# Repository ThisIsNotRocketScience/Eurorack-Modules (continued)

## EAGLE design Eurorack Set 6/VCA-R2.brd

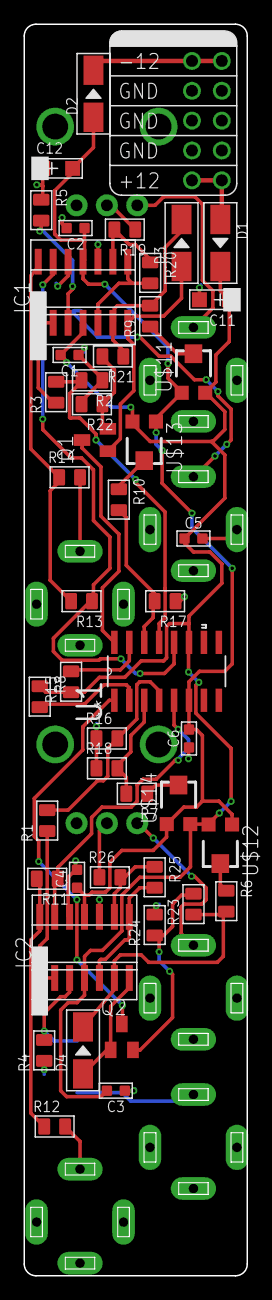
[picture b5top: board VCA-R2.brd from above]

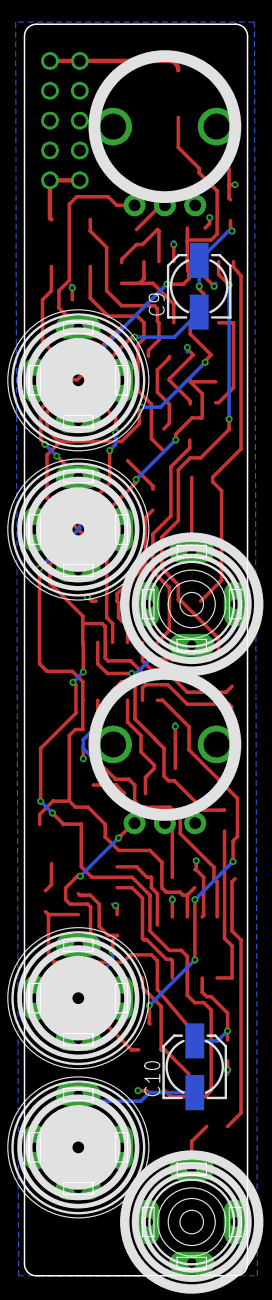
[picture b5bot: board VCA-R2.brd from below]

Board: 2 copper layers, 19.0 x 106.5 mm, 59 parts (11 on the bottom side), 43 nets.

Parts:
C1, C2, C3, C4, C5, C6: 100nF; C0603
C9, C10: 1uF-BIDIR; 153CLV-0505
C11, C12: 10uF; AVX-A
D1, D2, D3, D4: MRA4004T3G; DO-214AC
IC1, IC2: TL074D; SO14
Q1, Q2: MMBT3906LT1SMD; SOT23-BEC
R1, R3: 49.9K; C0805
R2, R16, R17, R18: 499; C0805
R4, R5, R6, R7, R9, R10: 220K; C0805
R8, R15: 249K; C0805
R11, R13: 30.1K; C0805
R12, R14: 100; C0805
R19, R26: 100K; C0805
R20, R21, R23, R25: 2K; C0805
R22, R24: 200; C0805
U1: LM13700M; SOIC127P620X175-16N
U$1: EURORACK_PCB4HP; EURORACK4HPPCB
U$2, U$3: 100K; OG-POTS_ALPS_POT_VERTICAL
U$4, U$5, U$6, U$7: PJ-341; 3.5MM-JACK-SWITCH-13MM-INPUT
U$8, U$9: PJ-341; 3.5MM-JACK-SWITCH-13MM-OUTPUT
U$10: POWER_SIMPLE10; POWER_10
U$11, U$12, U$13, U$14: 100K; TC33X

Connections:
12V: C1.2, C3.2, C5.1, C11.+, D1.2, IC1.4, IC2.4, R8.1, R15.1, U1.11, U$11.3, U$12.3, U$13.3, U$14.3
-12V: C2.1, C4.1, C6.2, C12.-, D2.1, IC1.11, IC2.11, U1.6, U$11.1, U$12.1, U$13.1, U$14.1
CV_IN_A: Q1.C, U1.16
CV_IN_B: Q2.C, U1.1
GND: C1.1, C2.2, C3.1, C4.2, C5.2, C6.1, C11.-, C12.+, IC1.10, IC1.12, IC2.10, IC2.12, R2.1, R4.1, R5.1, R16.1, R17.1, R18.1, R22.2, R24.2, U$2.P$3, U$3.P$3, U$4.RING@3, U$4.SWITCH@3, U$5.RING@3, U$5.SWITCH@3, U$6.RING@3, U$6.SWITCH@3, U$7.RING@3, U$7.SWITCH@3, U$8.RING@3, U$9.RING@3, U$10.3, U$10.4, U$10.5, U$10.6, U$10.7, U$10.8
unnamed: R14.2, U$8.TIP@3
unnamed: IC1.14, R13.2, R14.1
unnamed: R8.2, U1.2
unnamed: R15.2, U1.15
unnamed: R12.2, U$9.TIP@3
unnamed: IC2.14, R11.2, R12.1
unnamed: R19.1, U$2.P$2
unnamed: R10.1, U$13.2
unnamed: R9.1, U$11.2
unnamed: R7.1, U$14.2
unnamed: R6.1, U$12.2
unnamed: C9.-, U$4.TIP@3
unnamed: C10.-, U$6.TIP@3
unnamed: C9.+, IC1.3, R5.2
unnamed: C10.+, IC2.3, R4.2
unnamed: IC1.1, IC1.2, R3.1
unnamed: IC2.1, IC2.2, R1.1
unnamed: R2.2, R3.2, U1.13
unnamed: R1.2, R16.2, U1.4
unnamed: R10.2, R17.2, U1.14
unnamed: U$3.P$1, U$7.TIP@3
unnamed: R7.2, R18.2, U1.3
unnamed: U$2.P$1, U$5.TIP@3
unnamed: IC1.9, R19.2, R20.1
unnamed: IC1.5, IC1.8, R20.2
unnamed: D3.2, IC1.6, R9.2, R21.1
unnamed: D1.1, U$10.9, U$10.10
unnamed: D3.1, IC1.7, Q1.B
unnamed: Q1.E, R21.2, R22.1
unnamed: D4.2, IC2.6, R6.2, R23.1
unnamed: D4.1, IC2.7, Q2.B
unnamed: Q2.E, R23.2, R24.1
unnamed: IC2.5, IC2.8, R25.2
unnamed: R26.1, U$3.P$2
unnamed: IC2.9, R25.1, R26.2
unnamed: D2.2, U$10.1, U$10.2
TRANS_OUT_A: IC1.13, R13.1, U1.12
TRANS_OUT_B: IC2.13, R11.1, U1.5

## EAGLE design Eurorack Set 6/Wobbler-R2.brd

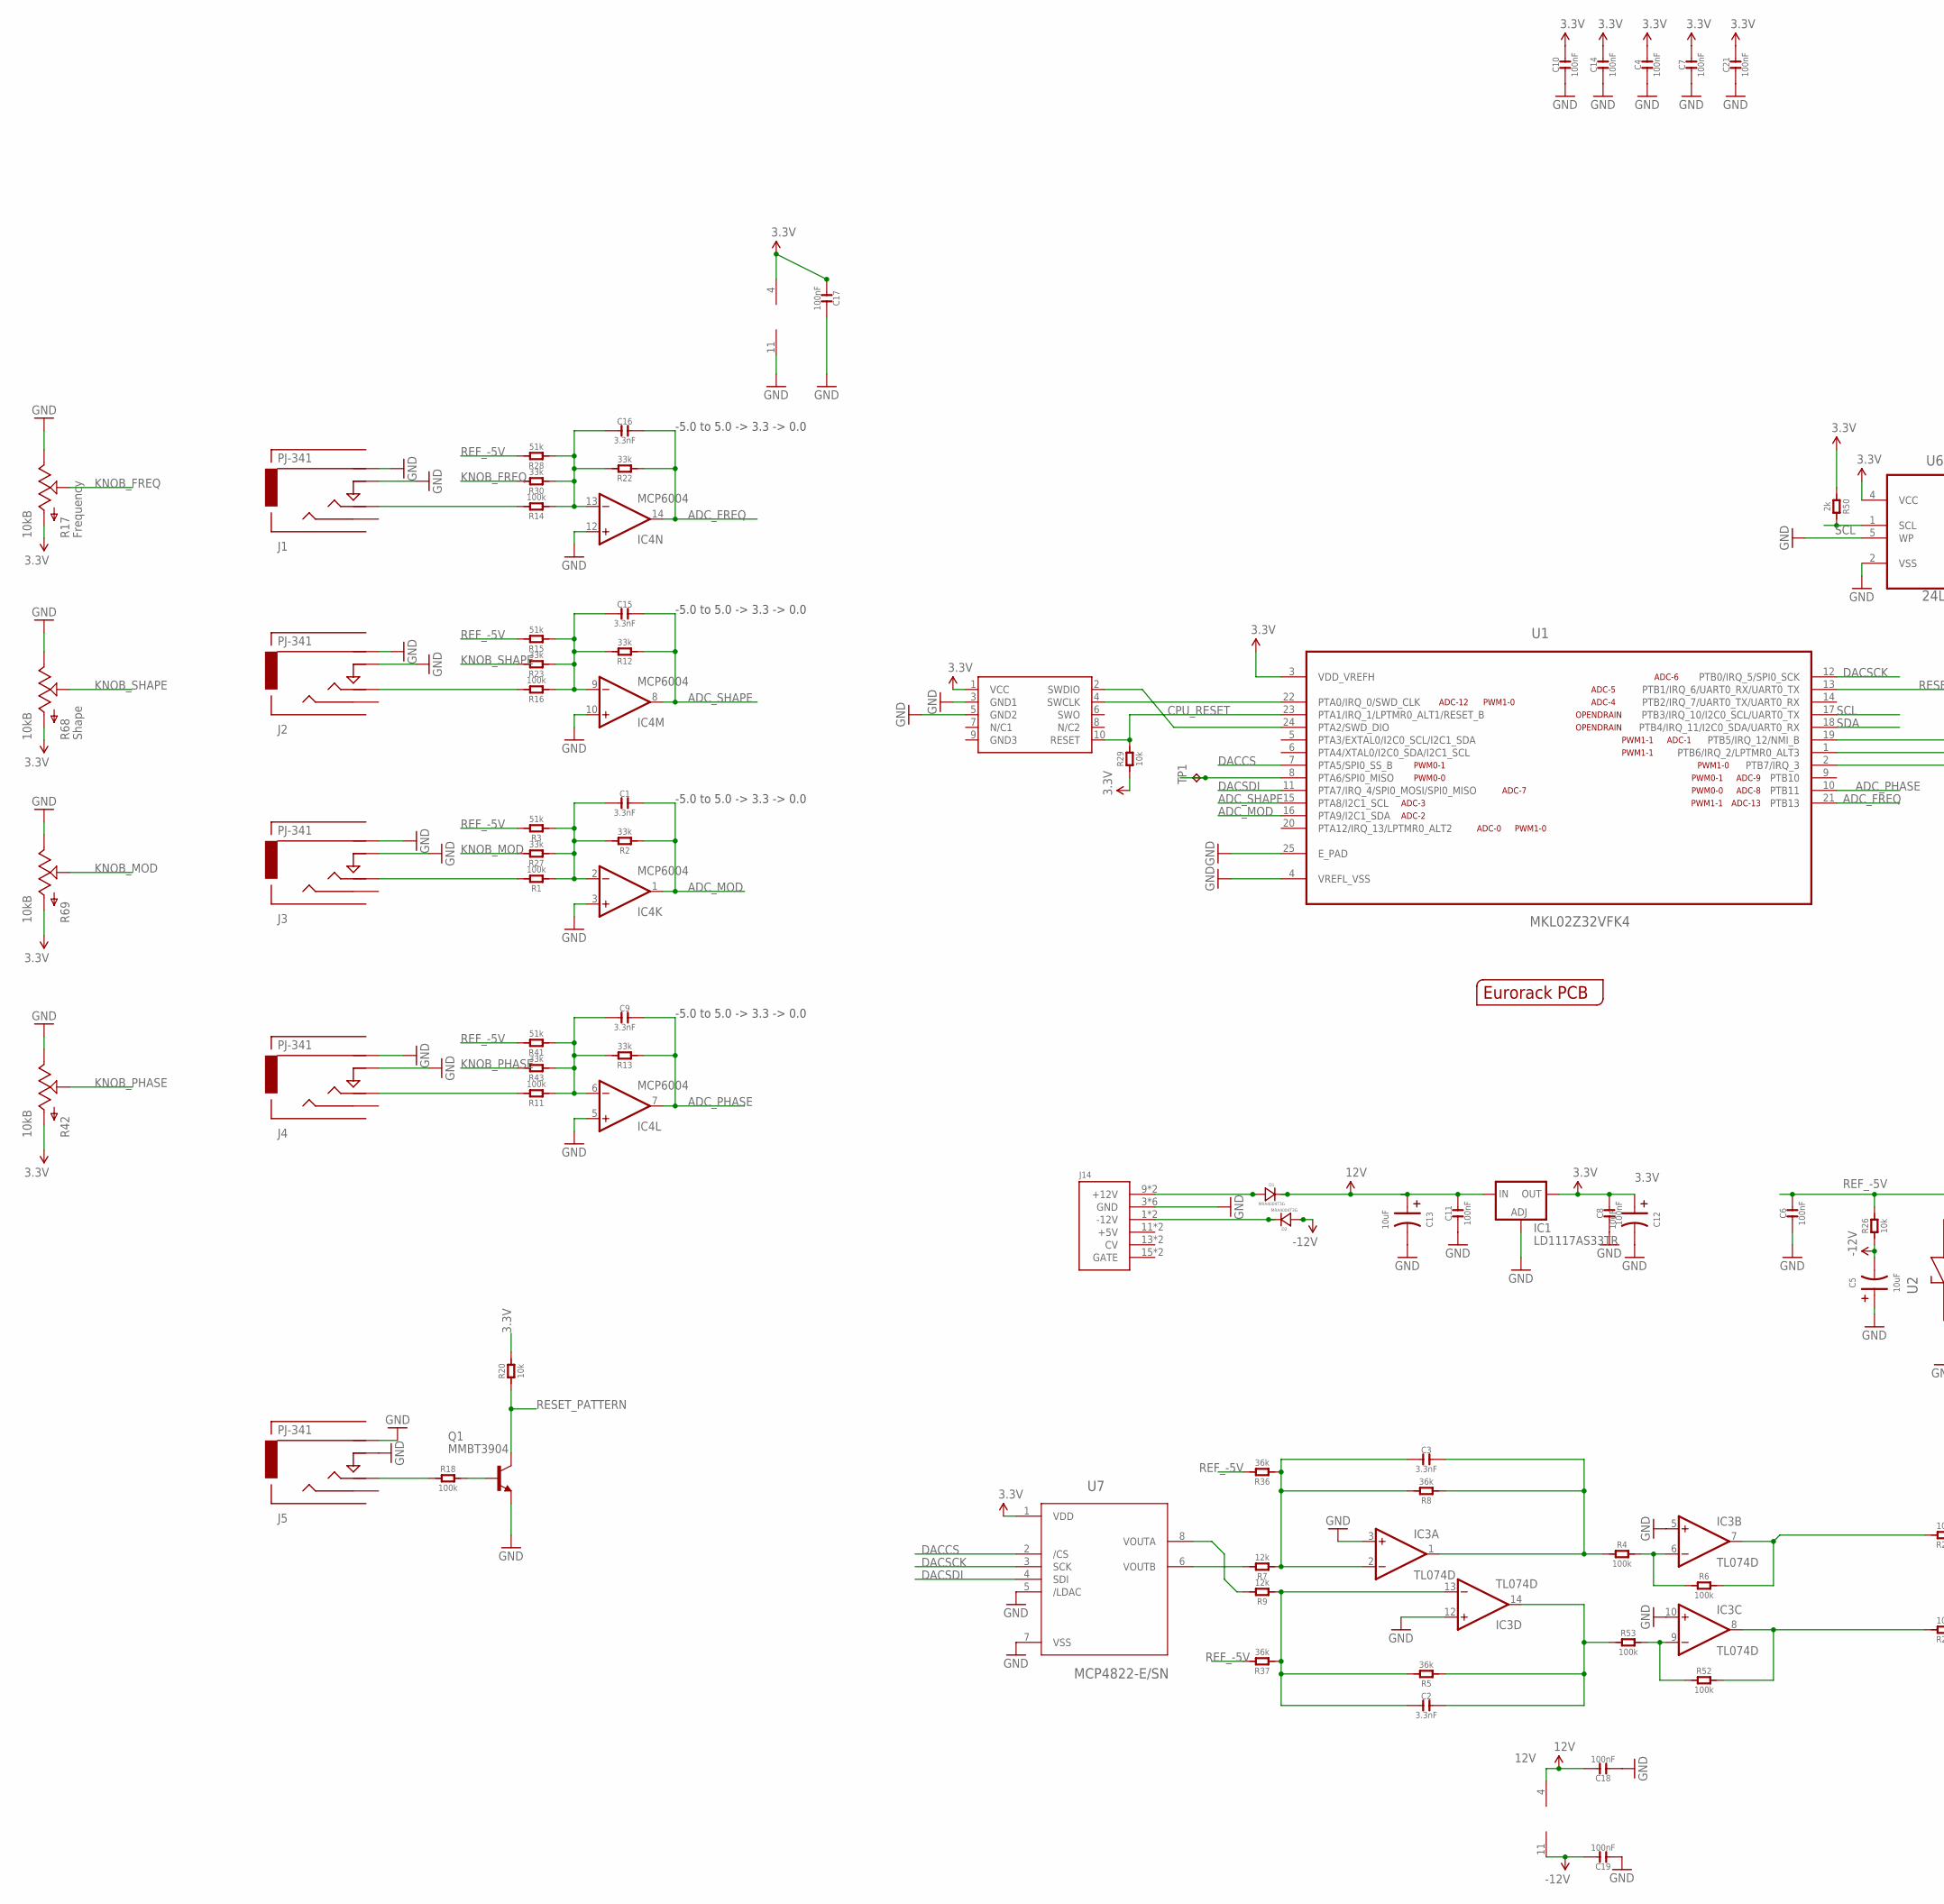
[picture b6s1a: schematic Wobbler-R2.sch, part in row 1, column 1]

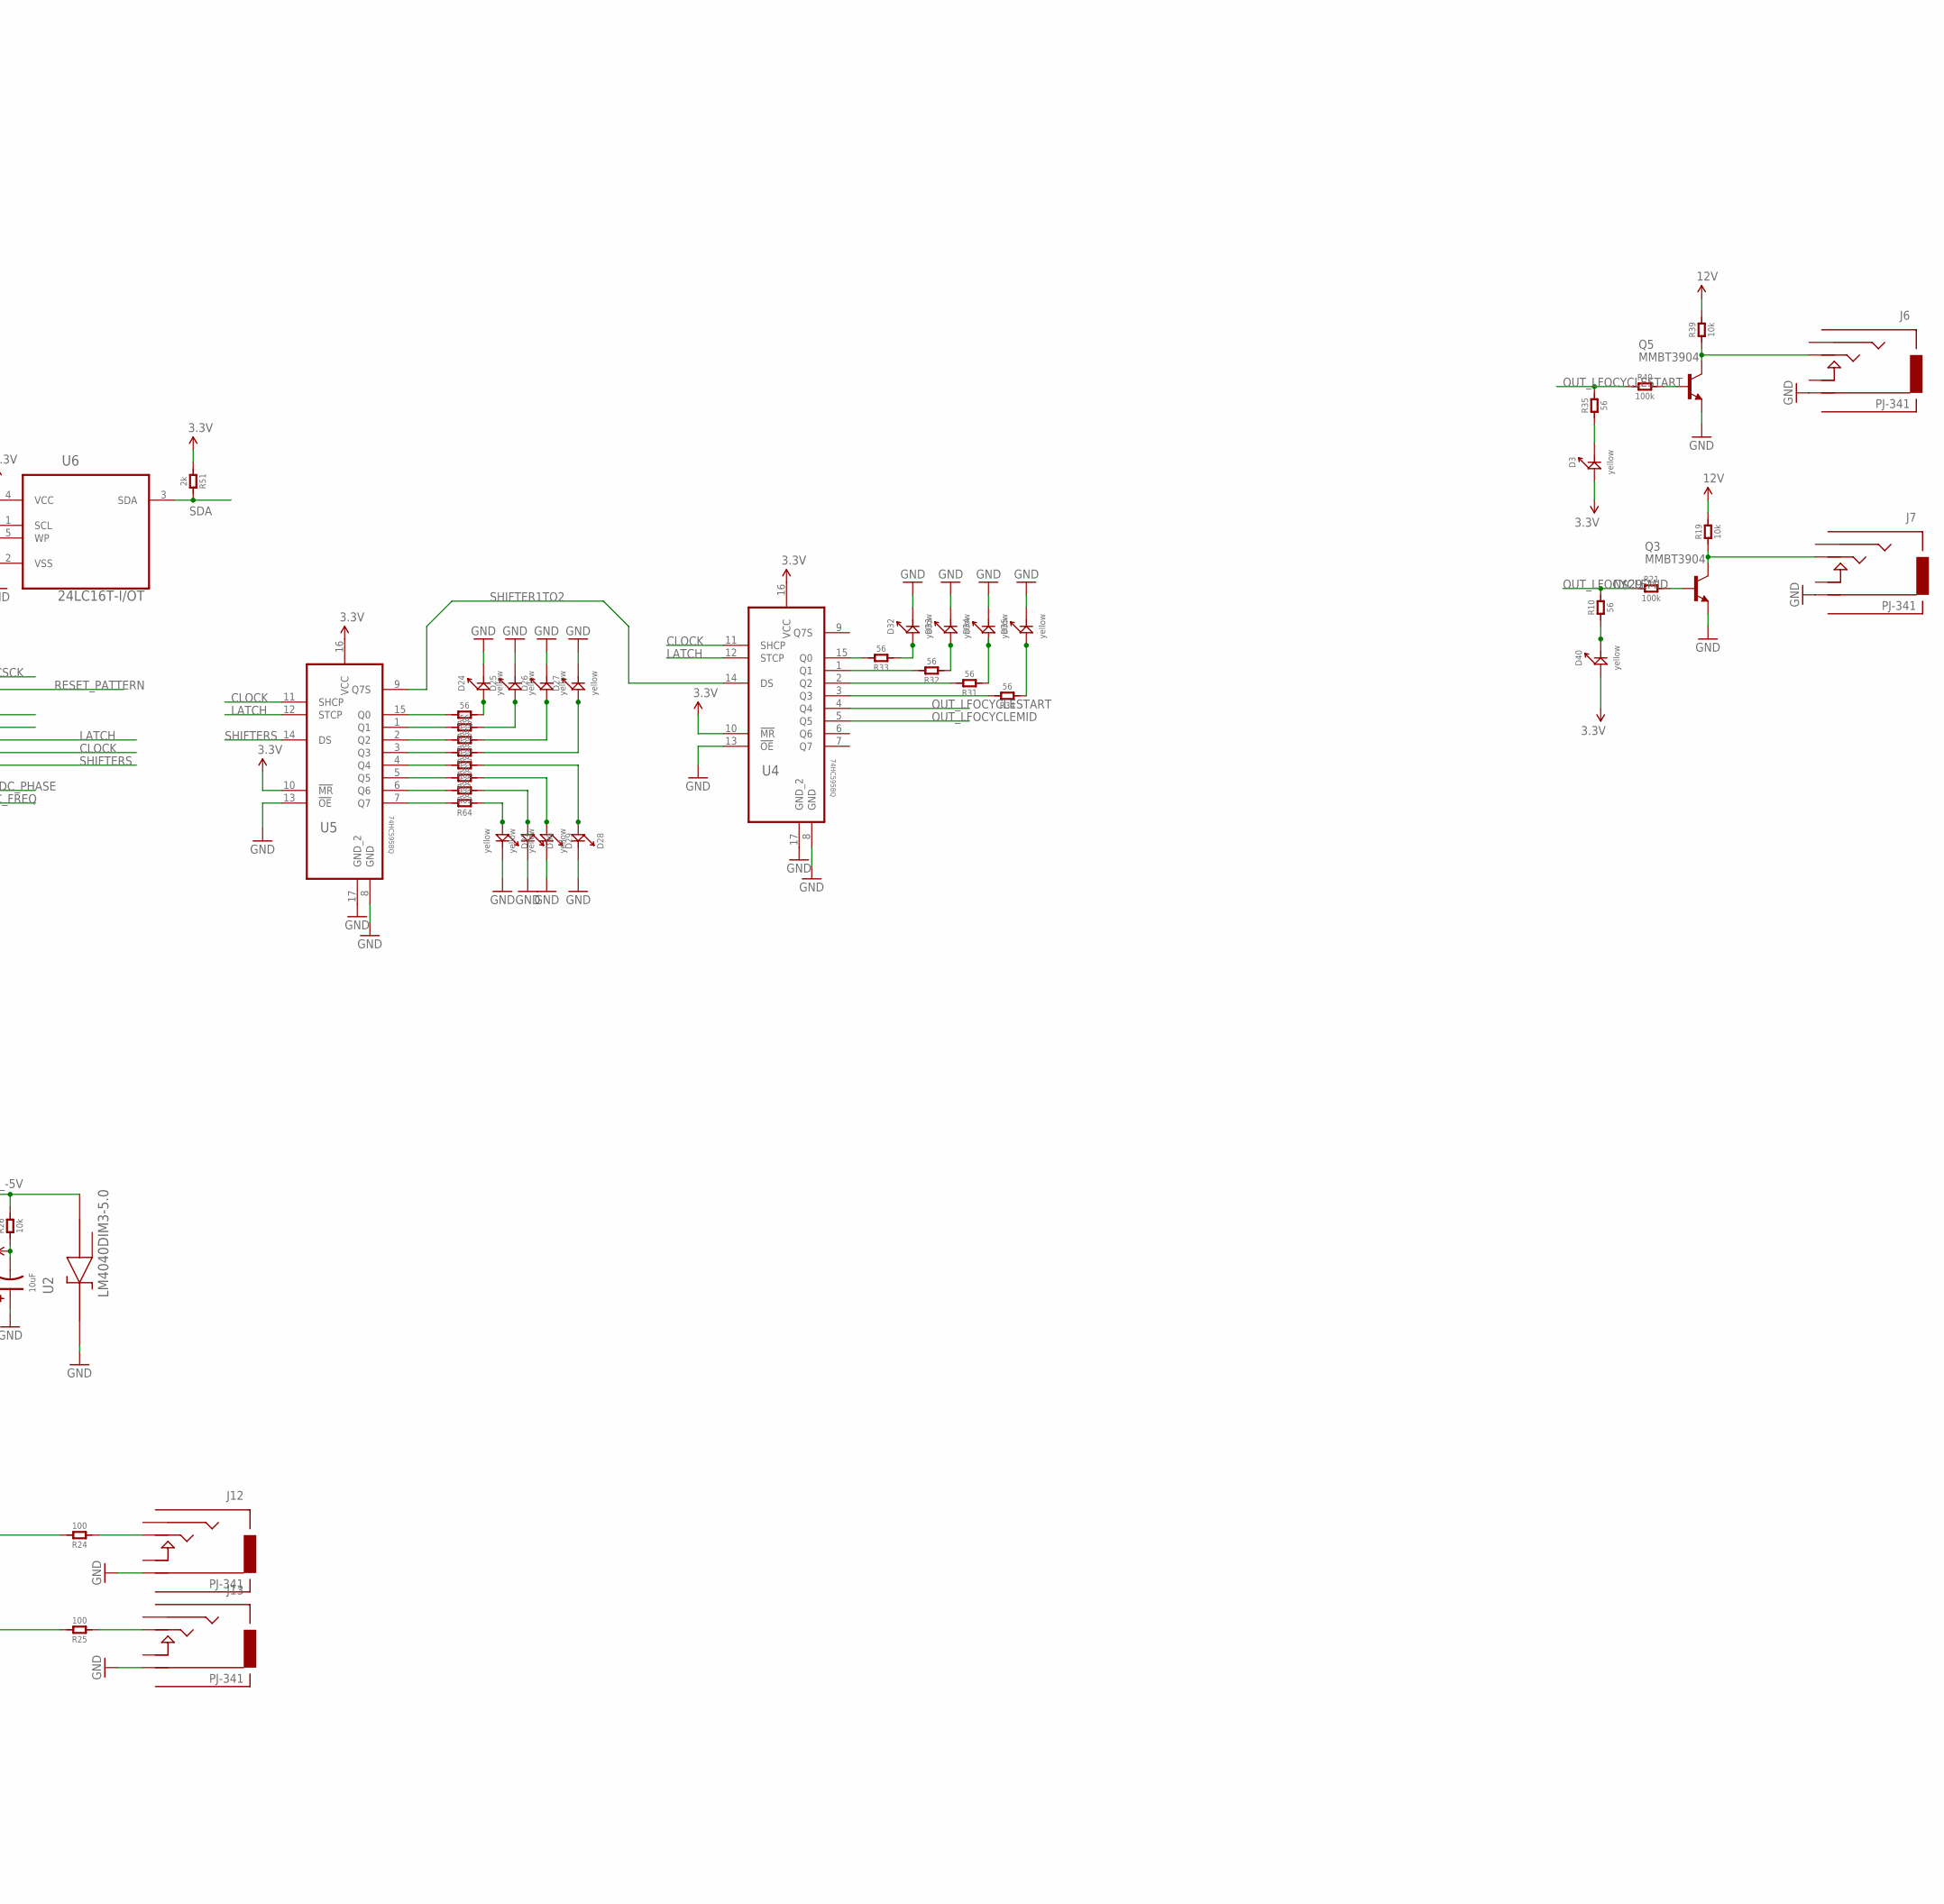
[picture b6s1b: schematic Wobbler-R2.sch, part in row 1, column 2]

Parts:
C1, C2, C3, C9, C15, C16: 3.3nF; C0603
C4, C7, C8, C10, C11, C14, C17, C18, C19, C21: 100nF; C0603; MPN MC0603F104Z160CT
C5, C12, C13: 10uF; AVX-A; MPN TAJB106K020RNJ
C6: 100nF; C0603; MPN 06035C104KAT2A
D1, D2: MRA4004T3G; DO-214AC; MPN US1G-E3/5AT
D3, D24, D25, D26, D27, D28, D29, D30, D31, D32, D33, D34, D35, D40: yellow; LED0603
IC1: LD1117AS33TR; SOT223; MPN LD1117AS33TR
IC3: TL074D; SO14; MPN TL074CD
IC4: MCP6004; SO14; MPN MCP6004-I/SL.
J1, J2, J3, J4, J5: PJ-341; 3.5MM-JACK-SWITCH-13MM-INPUT
J6, J7, J12, J13: PJ-341; 3.5MM-JACK-SWITCH-13MM-OUTPUT
J14: POWER; POWER_16
OUTLINE: EURORACK_PCB8HP; EURORACK8HPPCB
Q1, Q3, Q5: MMBT3904; SOT23-BEC; MPN PMBT3904,215
R1, R4, R6, R11, R14, R16, R18, R21, R40, R52, R53: 100k; R0603
R2, R12, R13, R22, R23, R27, R30, R43: 33k; R0603
R3, R15, R28, R41: 51k; R0603
R5, R8, R36, R37: 36k; R0603
R7, R9: 12k; R0603
R10, R31, R32, R33, R34, R35, R56, R57, R58, R59, R61, R62, R63, R64: 56; R0603
R17, R42, R68, R69: 10kB; OG-POTS_ALPS_POT_VERTICAL
R19, R20, R26, R29, R39: 10k; R0603
R24, R25: 100; R0603
R50, R51: 2k; R0603
SWD1: CORTEX_SWD; M50-3600542
TP1: TPB1,27; B1,27
U1: MKL02Z32VFK4; QFN50P400X400X100-25N
U2: LM4040DIM3-5.0; SOT95P237X112-3N
U4, U5: 74HC595BQ; QFN50P250X350X100-17N
U6: 24LC16T-I/OT; SOT95P290X145-5N; MPN 24LC00T-I/OT
U7: MCP4822-E/SN; SOIC8-N_MC

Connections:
3.3V: C4.2, C7.2, C8.2, C10.2, C12.+ (1), C14.2, C17.1, C21.2, D3.+, D40.+, IC1.2 (OUT), IC1.4 (OUT), IC4.4 (V+), R17.P$3 (A), R20.2, R29.1, R42.P$3 (A), R50.1, R51.1, R68.P$3 (A), R69.P$3 (A), SWD1.1 (VCC), U1.3 (VDD_VREFH), U4.10 (!MR), U4.16 (VCC), U5.10 (!MR), U5.16 (VCC), U6.4 (VCC), U7.1 (VDD)
12V: C11.2, C13.+ (1), C18.2, D1.2 (-), IC1.3 (IN), IC3.4 (V+), R19.2, R39.2
-12V: C5.- (2), C19.2, D2.1 (+), IC3.11 (V-), R26.1
ADC_FREQ: C16.2, IC4.14 (OUT), R22.1, U1.21 (PTB13)
ADC_MOD: C1.2, IC4.1 (OUT), R2.1, U1.16 (PTA9/I2C1_SDA)
ADC_PHASE: C9.2, IC4.7 (OUT), R13.1, U1.10 (PTB11)
ADC_SHAPE: C15.2, IC4.8 (OUT), R12.1, U1.15 (PTA8/I2C1_SCL)
CLOCK: U1.1 (PTB6/IRQ_2/LPTMR0_ALT3), U4.11 (SHCP), U5.11 (SHCP)
CPU_RESET: R29.2, SWD1.10 (RESET), U1.23 (PTA1/IRQ_1/LPTMR0_ALT1/RESET_B)
DACCS: U1.7 (PTA5/SPI0_SS_B), U7.2 (/CS)
DACSCK: U1.12 (PTB0/IRQ_5/SPI0_SCK), U7.3 (SCK)
DACSDI: U1.11 (PTA7/IRQ_4/SPI0_MOSI/SPI0_MISO), U7.4 (SDI)
GND: C4.1, C5.+ (1), C6.1, C7.1, C8.1, C10.1, C11.1, C12.- (2), C13.- (2), C14.1, C17.2, C18.1, C19.1, C21.1, D24.-, D25.-, D26.-, D27.-, D28.-, D29.-, D30.-, D31.-, D32.-, D33.-, D34.-, D35.-, IC1.1 (ADJ), IC3.3 (+IN), IC3.5 (+IN), IC3.10 (+IN), IC3.12 (+IN), IC4.3 (+IN), IC4.5 (+IN), IC4.10 (+IN), IC4.11 (V-), IC4.12 (+IN), J1.RING@3 (RING), J1.SWITCH@3 (SWITCH), J2.RING@3 (RING), J2.SWITCH@3 (SWITCH), J3.RING@3 (RING), J3.SWITCH@3 (SWITCH), J4.RING@3 (RING), J4.SWITCH@3 (SWITCH), J5.RING@3 (RING), J5.SWITCH@3 (SWITCH), J6.RING@3 (RING), J7.RING@3 (RING), J12.RING@3 (RING), J13.RING@3 (RING), J14.3 (GND), J14.4 (GND), J14.5 (GND), J14.6 (GND), J14.7 (GND), J14.8 (GND), Q1.E, Q3.E, Q5.E, R17.P$1 (E), R42.P$1 (E), R68.P$1 (E), R69.P$1 (E), SWD1.3 (GND1), SWD1.5 (GND2), U1.4 (VREFL_VSS), U1.25 (E_PAD), U2.1 (CATHODE), U4.8 (GND), U4.13 (!OE), U4.17 (GND_2), U5.8 (GND), U5.13 (!OE), U5.17 (GND_2), U6.2 (VSS), U6.5 (WP), U7.5 (/LDAC), U7.7 (VSS)
KNOB_FREQ: R17.P$2 (S), R30.2
KNOB_MOD: R27.2, R69.P$2 (S)
KNOB_PHASE: R42.P$2 (S), R43.2
KNOB_SHAPE: R23.2, R68.P$2 (S)
LATCH: U1.19 (PTB5/IRQ_12/NMI_B), U4.12 (STCP), U5.12 (STCP)
unnamed: R33.2, U4.15 (Q0)
unnamed: IC3.6 (-IN), R4.2, R6.1
unnamed: J2.TIP@3 (TIP), R16.2
unnamed: C15.1, IC4.9 (-IN), R12.2, R15.1, R16.1, R23.1
unnamed: R9.2, U7.8 (VOUTA)
unnamed: J3.TIP@3 (TIP), R1.2
unnamed: R7.2, U7.6 (VOUTB)
unnamed: C1.1, IC4.2 (-IN), R1.1, R2.2, R3.1, R27.1
unnamed: C2.1, IC3.13 (-IN), R5.2, R9.1, R37.1
unnamed: C3.1, IC3.2 (-IN), R7.1, R8.2, R36.1
unnamed: J4.TIP@3 (TIP), R11.2
unnamed: C9.1, IC4.6 (-IN), R11.1, R13.2, R41.1, R43.1
unnamed: D1.1 (+), J14.9 (+12V), J14.10 (+12V)
unnamed: IC3.7 (OUT), R6.2, R24.2
unnamed: Q1.B, R18.2
unnamed: J5.TIP@3 (TIP), R18.1
unnamed: IC3.9 (-IN), R52.1, R53.2
unnamed: C3.2, IC3.1 (OUT), R4.1, R8.1
unnamed: R32.2, U4.1 (Q1)
unnamed: J13.TIP@3 (TIP), R25.1
unnamed: J12.TIP@3 (TIP), R24.1
unnamed: R59.2, U5.15 (Q0)
unnamed: D40.-, R10.1
unnamed: C2.2, IC3.14 (OUT), R5.1, R53.1
unnamed: Q3.B, R21.2
unnamed: R31.2, U4.2 (Q2)
unnamed: D3.-, R35.1
unnamed: D28.+, R62.1
unnamed: J7.TIP@3 (TIP), Q3.C, R19.1
unnamed: R58.2, U5.1 (Q1)
unnamed: R56.2, U5.2 (Q2)
unnamed: D29.+, R61.1
unnamed: J1.TIP@3 (TIP), R14.2
unnamed: C16.1, IC4.13 (-IN), R14.1, R22.2, R28.1, R30.1
unnamed: R57.2, U5.3 (Q3)
unnamed: R34.2, U4.3 (Q3)
unnamed: R62.2, U5.4 (Q4)
unnamed: R61.2, U5.5 (Q5)
unnamed: R63.2, U5.6 (Q6)
unnamed: R64.2, U5.7 (Q7)
unnamed: Q5.B, R40.2
unnamed: J6.TIP@3 (TIP), Q5.C, R39.1
unnamed: D2.2 (-), J14.1 (-12V), J14.2 (-12V)
unnamed: D27.+, R57.1
unnamed: D26.+, R56.1
unnamed: D25.+, R58.1
unnamed: D24.+, R59.1
unnamed: D30.+, R63.1
unnamed: D31.+, R64.1
unnamed: D32.+, R33.1
unnamed: D33.+, R32.1
unnamed: D34.+, R31.1
unnamed: D35.+, R34.1
unnamed: IC3.8 (OUT), R25.2, R52.2
OUT_LFOCYCLEMID: R10.2, R21.1, U4.5 (Q5)
OUT_LFOCYCLESTART: R35.2, R40.1, U4.4 (Q4)
PTA6: TP1.TP, U1.8 (PTA6/SPI0_MISO)
REF_-5V: C6.2, R3.2, R15.2, R26.2, R28.2, R36.2, R37.2, R41.2, U2.2 (ANODE)
RESET_PATTERN: Q1.C, R20.1, U1.13 (PTB1/IRQ_6/UART0_RX/UART0_TX)
SCL: R50.2, U1.17 (PTB3/IRQ_10/I2C0_SCL/UART0_TX), U6.1 (SCL)
SDA: R51.2, U1.18 (PTB4/IRQ_11/I2C0_SDA/UART0_RX), U6.3 (SDA)
SHIFTER1TO2: U4.14 (DS), U5.9 (Q7S)
SHIFTERS: U1.2 (PTB7/IRQ_3), U5.14 (DS)
SWD_CLK: SWD1.4 (SWCLK), U1.22 (PTA0/IRQ_0/SWD_CLK)
SWD_DIO: SWD1.2 (SWDIO), U1.24 (PTA2/SWD_DIO)

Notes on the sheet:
-5.0 to 5.0 -> 3.3 -> 0.0

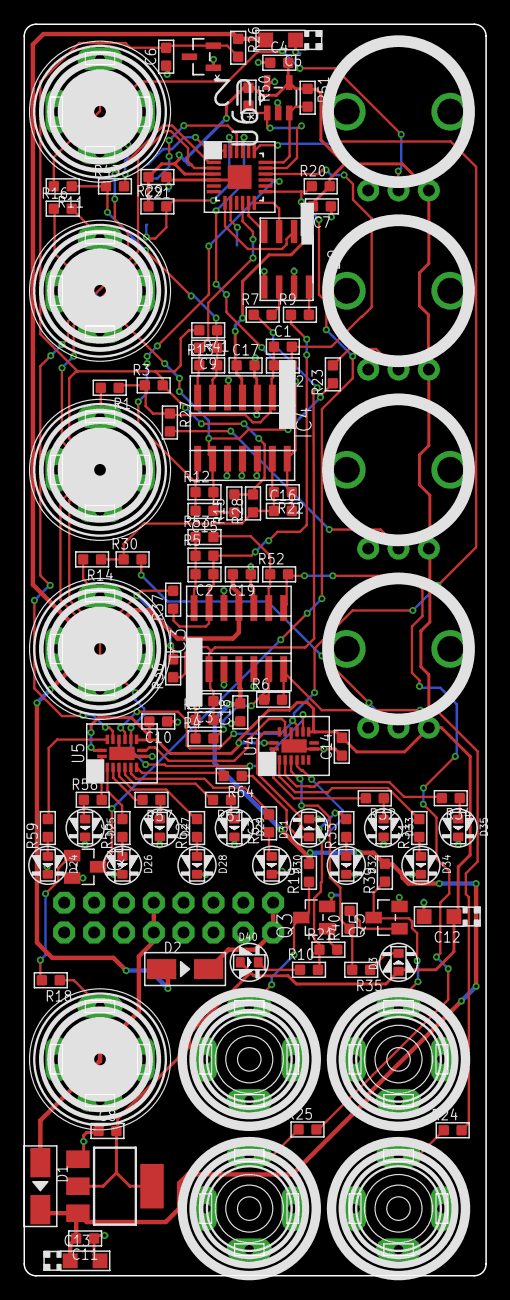
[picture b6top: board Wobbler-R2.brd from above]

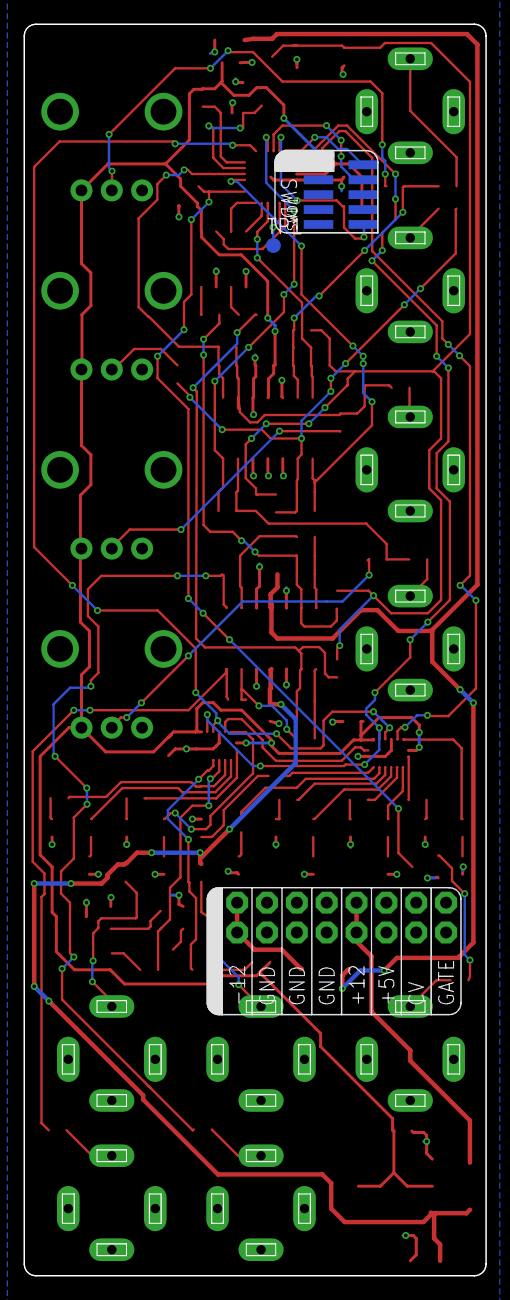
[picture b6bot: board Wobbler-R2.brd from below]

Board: 2 copper layers, 39.3 x 106.5 mm, 117 parts (3 on the bottom side), 83 nets.

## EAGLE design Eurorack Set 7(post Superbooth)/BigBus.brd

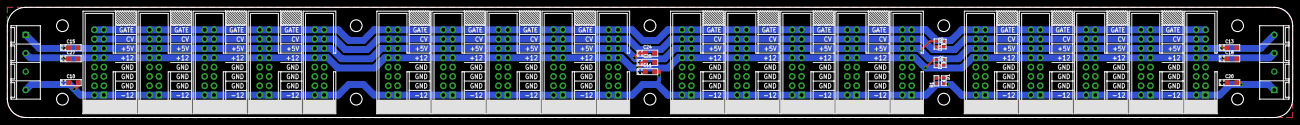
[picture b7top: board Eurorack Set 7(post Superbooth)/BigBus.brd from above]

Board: 2 copper layers, 350.0 x 30.0 mm, 47 parts (0 on the bottom side), 9 nets.

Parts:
C10, C11, C13, C15, C18, C20, C24, C25, C27: 10u; AVX-A
D1, D2, D3: yellow; LED0603
H1, H2, H3, H4, H5, H6, H7, H8, H9, H10: MOUNT-HOLE; 3.2-NOMARKINGS-SMALLSAFEZONE
R1, R2: 680; R0603
R3: 220; R0603
U$1, U$3, U$4, U$5, U$6, U$8, U$9, U$10, U$11, U$12, U$13, U$14, U$15, U$16, U$17, U$20: POWERSHROUDED; POWER_16_SHROUDED
U$2, U$7, U$18, U$21: POWER_SHROUDED_NOTEXT; POWER_16_SHROUDED_NOTEXT
U$19, U$22: 4PIN5MM

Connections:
+5: C13.+, C15.+, C24.+, R3.1, U$1.11, U$1.12, U$2.11, U$2.12, U$3.11, U$3.12, U$4.11, U$4.12, U$5.11, U$5.12, U$6.11, U$6.12, U$7.11, U$7.12, U$8.11, U$8.12, U$9.11, U$9.12, U$10.11, U$10.12, U$11.11, U$11.12, U$12.11, U$12.12, U$13.11, U$13.12, U$14.11, U$14.12, U$15.11, U$15.12, U$16.11, U$16.12, U$17.11, U$17.12, U$18.11, U$18.12, U$19.4, U$20.11, U$20.12, U$21.11, U$21.12, U$22.1
+12: C18.+, C25.+, C27.+, R2.1, U$1.9, U$1.10, U$2.9, U$2.10, U$3.9, U$3.10, U$4.9, U$4.10, U$5.9, U$5.10, U$6.9, U$6.10, U$7.9, U$7.10, U$8.9, U$8.10, U$9.9, U$9.10, U$10.9, U$10.10, U$11.9, U$11.10, U$12.9, U$12.10, U$13.9, U$13.10, U$14.9, U$14.10, U$15.9, U$15.10, U$16.9, U$16.10, U$17.9, U$17.10, U$18.9, U$18.10, U$19.3, U$20.9, U$20.10, U$21.9, U$21.10, U$22.2
-12: C10.-, C11.-, C20.-, D1.-, U$1.1, U$1.2, U$2.1, U$2.2, U$3.1, U$3.2, U$4.1, U$4.2, U$5.1, U$5.2, U$6.1, U$6.2, U$7.1, U$7.2, U$8.1, U$8.2, U$9.1, U$9.2, U$10.1, U$10.2, U$11.1, U$11.2, U$12.1, U$12.2, U$13.1, U$13.2, U$14.1, U$14.2, U$15.1, U$15.2, U$16.1, U$16.2, U$17.1, U$17.2, U$18.1, U$18.2, U$19.1, U$20.1, U$20.2, U$21.1, U$21.2, U$22.4
CV: U$1.13, U$1.14, U$2.13, U$2.14, U$3.13, U$3.14, U$4.13, U$4.14, U$5.13, U$5.14, U$6.13, U$6.14, U$7.13, U$7.14, U$8.13, U$8.14, U$9.13, U$9.14, U$10.13, U$10.14, U$11.13, U$11.14, U$12.13, U$12.14, U$13.13, U$13.14, U$14.13, U$14.14, U$15.13, U$15.14, U$16.13, U$16.14, U$17.13, U$17.14, U$18.13, U$18.14, U$20.13, U$20.14, U$21.13, U$21.14
GATE: U$1.15, U$1.16, U$2.15, U$2.16, U$3.15, U$3.16, U$4.15, U$4.16, U$5.15, U$5.16, U$6.15, U$6.16, U$7.15, U$7.16, U$8.15, U$8.16, U$9.15, U$9.16, U$10.15, U$10.16, U$11.15, U$11.16, U$12.15, U$12.16, U$13.15, U$13.16, U$14.15, U$14.16, U$15.15, U$15.16, U$16.15, U$16.16, U$17.15, U$17.16, U$18.15, U$18.16, U$20.15, U$20.16, U$21.15, U$21.16
GND: C10.+, C11.+, C13.-, C15.-, C18.-, C20.+, C24.-, C25.-, C27.-, D2.-, D3.-, R1.1, U$1.3, U$1.4, U$1.5, U$1.6, U$1.7, U$1.8, U$2.3, U$2.4, U$2.5, U$2.6, U$2.7, U$2.8, U$3.3, U$3.4, U$3.5, U$3.6, U$3.7, U$3.8, U$4.3, U$4.4, U$4.5, U$4.6, U$4.7, U$4.8, U$5.3, U$5.4, U$5.5, U$5.6, U$5.7, U$5.8, U$6.3, U$6.4, U$6.5, U$6.6, U$6.7, U$6.8, U$7.3, U$7.4, U$7.5, U$7.6, U$7.7, U$7.8, U$8.3, U$8.4, U$8.5, U$8.6, U$8.7, U$8.8, U$9.3, U$9.4, U$9.5, U$9.6, U$9.7, U$9.8, U$10.3, U$10.4, U$10.5, U$10.6, U$10.7, U$10.8, U$11.3, U$11.4, U$11.5, U$11.6, U$11.7, U$11.8, U$12.3, U$12.4, U$12.5, U$12.6, U$12.7, U$12.8, U$13.3, U$13.4, U$13.5, U$13.6, U$13.7, U$13.8, U$14.3, U$14.4, U$14.5, U$14.6, U$14.7, U$14.8, U$15.3, U$15.4, U$15.5, U$15.6, U$15.7, U$15.8, U$16.3, U$16.4, U$16.5, U$16.6, U$16.7, U$16.8, U$17.3, U$17.4, U$17.5, U$17.6, U$17.7, U$17.8, U$18.3, U$18.4, U$18.5, U$18.6, U$18.7, U$18.8, U$19.2, U$20.3, U$20.4, U$20.5, U$20.6, U$20.7, U$20.8, U$21.3, U$21.4, U$21.5, U$21.6, U$21.7, U$21.8, U$22.3
unnamed: D1.+, R1.2
unnamed: D2.+, R2.2
unnamed: D3.+, R3.2
